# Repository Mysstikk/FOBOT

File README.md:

# FOBOT — Feeding Collaborative Robot

FOBOT es un prototipo de robot colaborativo de seis grados de libertad diseñado para asistir durante la alimentación de personas con movilidad reducida o diversidad funcional.

El sistema combina actuadores Dynamixel, ROS 2, MoveIt 2 y visión artificial para ejecutar una secuencia de recogida de comida y aproximar una cuchara a la boca del usuario mediante control visual.

Este repositorio contiene el código fuente desarrollado para el Trabajo de Fin de Grado:

> *Design and implementation of a collaborative robot for feeding with control through artificial vision*

Autor: Unai Mollá Caballero  
Tutor: Jaime Masiá Vañó  
Universitat Politècnica de València — Campus d'Alcoi  
Curso: 2025–2026

## Características principales

- Control de seis actuadores Dynamixel.
- Integración del hardware mediante `ros2_control`.
- Ejecución de trayectorias articulares previamente configuradas.
- Grabación de posiciones mediante guiado manual.
- Coordinación del comportamiento mediante una máquina de estados finitos.
- Detección facial mediante MediaPipe.
- Reconocimiento de la apertura de la boca y el cierre de los ojos.
- Estimación tridimensional de la posición de la boca.
- Aproximación mediante MoveIt Servo.
- Supervisión de singularidades y colisiones.
- Detección de posibles contactos mediante el esfuerzo de los motores.
- Interfaz física mediante pulsadores e indicadores LED.

## Arquitectura del repositorio

```text
FOBOT/
├── robot_pkg/                 # Control principal, FSM y movimientos
├── fobot_moveit_config/       # Configuración de MoveIt 2
├── fobot_vision/              # Detección facial y control visual
├── singularity_probe/         # Análisis del jacobiano
├── DynamixelSDK               # SDK de los motores Dynamixel
├── dynamixel_interfaces/      # Mensajes y servicios de Dynamixel
├── dynamixel_hardware_interface/
│                              # Integración con ros2_control
└── README.md
```

La estructura puede variar dependiendo de la versión publicada.

## Requisitos

El sistema se ha desarrollado utilizando:

- Ubuntu 22.04.
- ROS 2 Humble.
- Python 3.
- C++.
- MoveIt 2.
- `ros2_control`.
- Dynamixel SDK.
- OpenCV.
- MediaPipe.
- Cámara USB.
- Raspberry Pi 4.

También se necesitan los paquetes de ROS 2 correspondientes a MoveIt Servo, TF2, `usb_cam` y el controlador de trayectorias articulares.

## Instalación

Crear un espacio de trabajo de ROS 2:

```bash
mkdir -p ~/fobot_ws/src
cd ~/fobot_ws/src
```

Clonar el repositorio:

```bash
git clone <URL_DEL_REPOSITORIO>
```

Instalar las dependencias:

```bash
cd ~/fobot_ws
rosdep install --from-paths src --ignore-src -r -y
```

Compilar:

```bash
colcon build --symlink-install
source install/setup.bash
```

La instrucción `source install/setup.bash` debe ejecutarse en cada nueva terminal desde la que se utilice el robot.

## Configuración previa

Antes de iniciar el sistema se debe comprobar:

1. Que cada motor Dynamixel tenga un identificador diferente.
2. Que el puerto serie y la velocidad de comunicación sean correctos.
3. Que la cámara esté conectada y calibrada.
4. Que el plato y el robot estén situados en las posiciones utilizadas durante la configuración.
5. Que la cuchara esté limpia y correctamente fijada.
6. Que no haya obstáculos dentro del espacio de trabajo.

Los parámetros principales se encuentran en los archivos YAML de los paquetes correspondientes.

## Ejecución

Para iniciar el sistema completo:

```bash
ros2 launch robot_pkg FOBOT.launch.py
```

El fichero maestro inicia los controladores, la descripción del robot, la máquina de estados, el sistema de visión y MoveIt Servo.

Después del arranque se debe realizar el movimiento de *homing* antes de comenzar la secuencia de alimentación.

## Grabación de trayectorias

El movimiento automático utiliza una secuencia de posiciones articulares almacenada en un fichero CSV.

El programa de grabación permite:

1. Desactivar el par de los motores.
2. Mover manualmente el brazo.
3. Registrar las posiciones deseadas.
4. Volver a activar el par.
5. Probar la trayectoria antes de utilizarla con comida.

Las primeras pruebas deben realizarse sin situar al usuario dentro del alcance inmediato del robot.

## Funcionamiento general

La secuencia de alimentación es la siguiente:

1. El robot realiza el movimiento de *homing*.
2. El usuario abre la boca para iniciar el ciclo.
3. El robot ejecuta la trayectoria de recogida.
4. La cuchara se desplaza hasta una posición próxima al rostro.
5. El usuario vuelve a abrir la boca para confirmar la entrega.
6. El sistema de visión estima la posición de la boca.
7. MoveIt Servo realiza la aproximación final.
8. El robot regresa para recoger una nueva porción.
9. El usuario puede finalizar el proceso cerrando ambos ojos.

## Limitaciones

El prototipo presenta actualmente las siguientes limitaciones:

- No detecta automáticamente la comida presente en el plato.
- La recogida utiliza trayectorias previamente grabadas.
- El plato debe permanecer en una posición aproximadamente fija.
- La profundidad se estima mediante una cámara RGB monocular.
- El comportamiento puede verse afectado por la iluminación y las oclusiones.
- No se ha realizado una validación clínica ni una certificación de seguridad.
- El sistema debe utilizarse en un entorno controlado y con supervisión.

## Seguridad

Este software pertenece a un prototipo académico y no constituye un producto médico o asistencial certificado.

Antes de utilizarlo:

- Mantener despejado el espacio de trabajo.
- No introducir las manos mientras los motores estén activos.
- Comprobar la temperatura y consistencia de la comida.
- Verificar la fijación de la cuchara.
- No rearmar el sistema sin identificar la causa de la parada.
- Utilizar el interruptor de alimentación si el robot presenta un comportamiento inesperado.

El uso del código y del prototipo se realiza bajo la responsabilidad de la persona que lo instala y opera.

Unai Mollá Caballero

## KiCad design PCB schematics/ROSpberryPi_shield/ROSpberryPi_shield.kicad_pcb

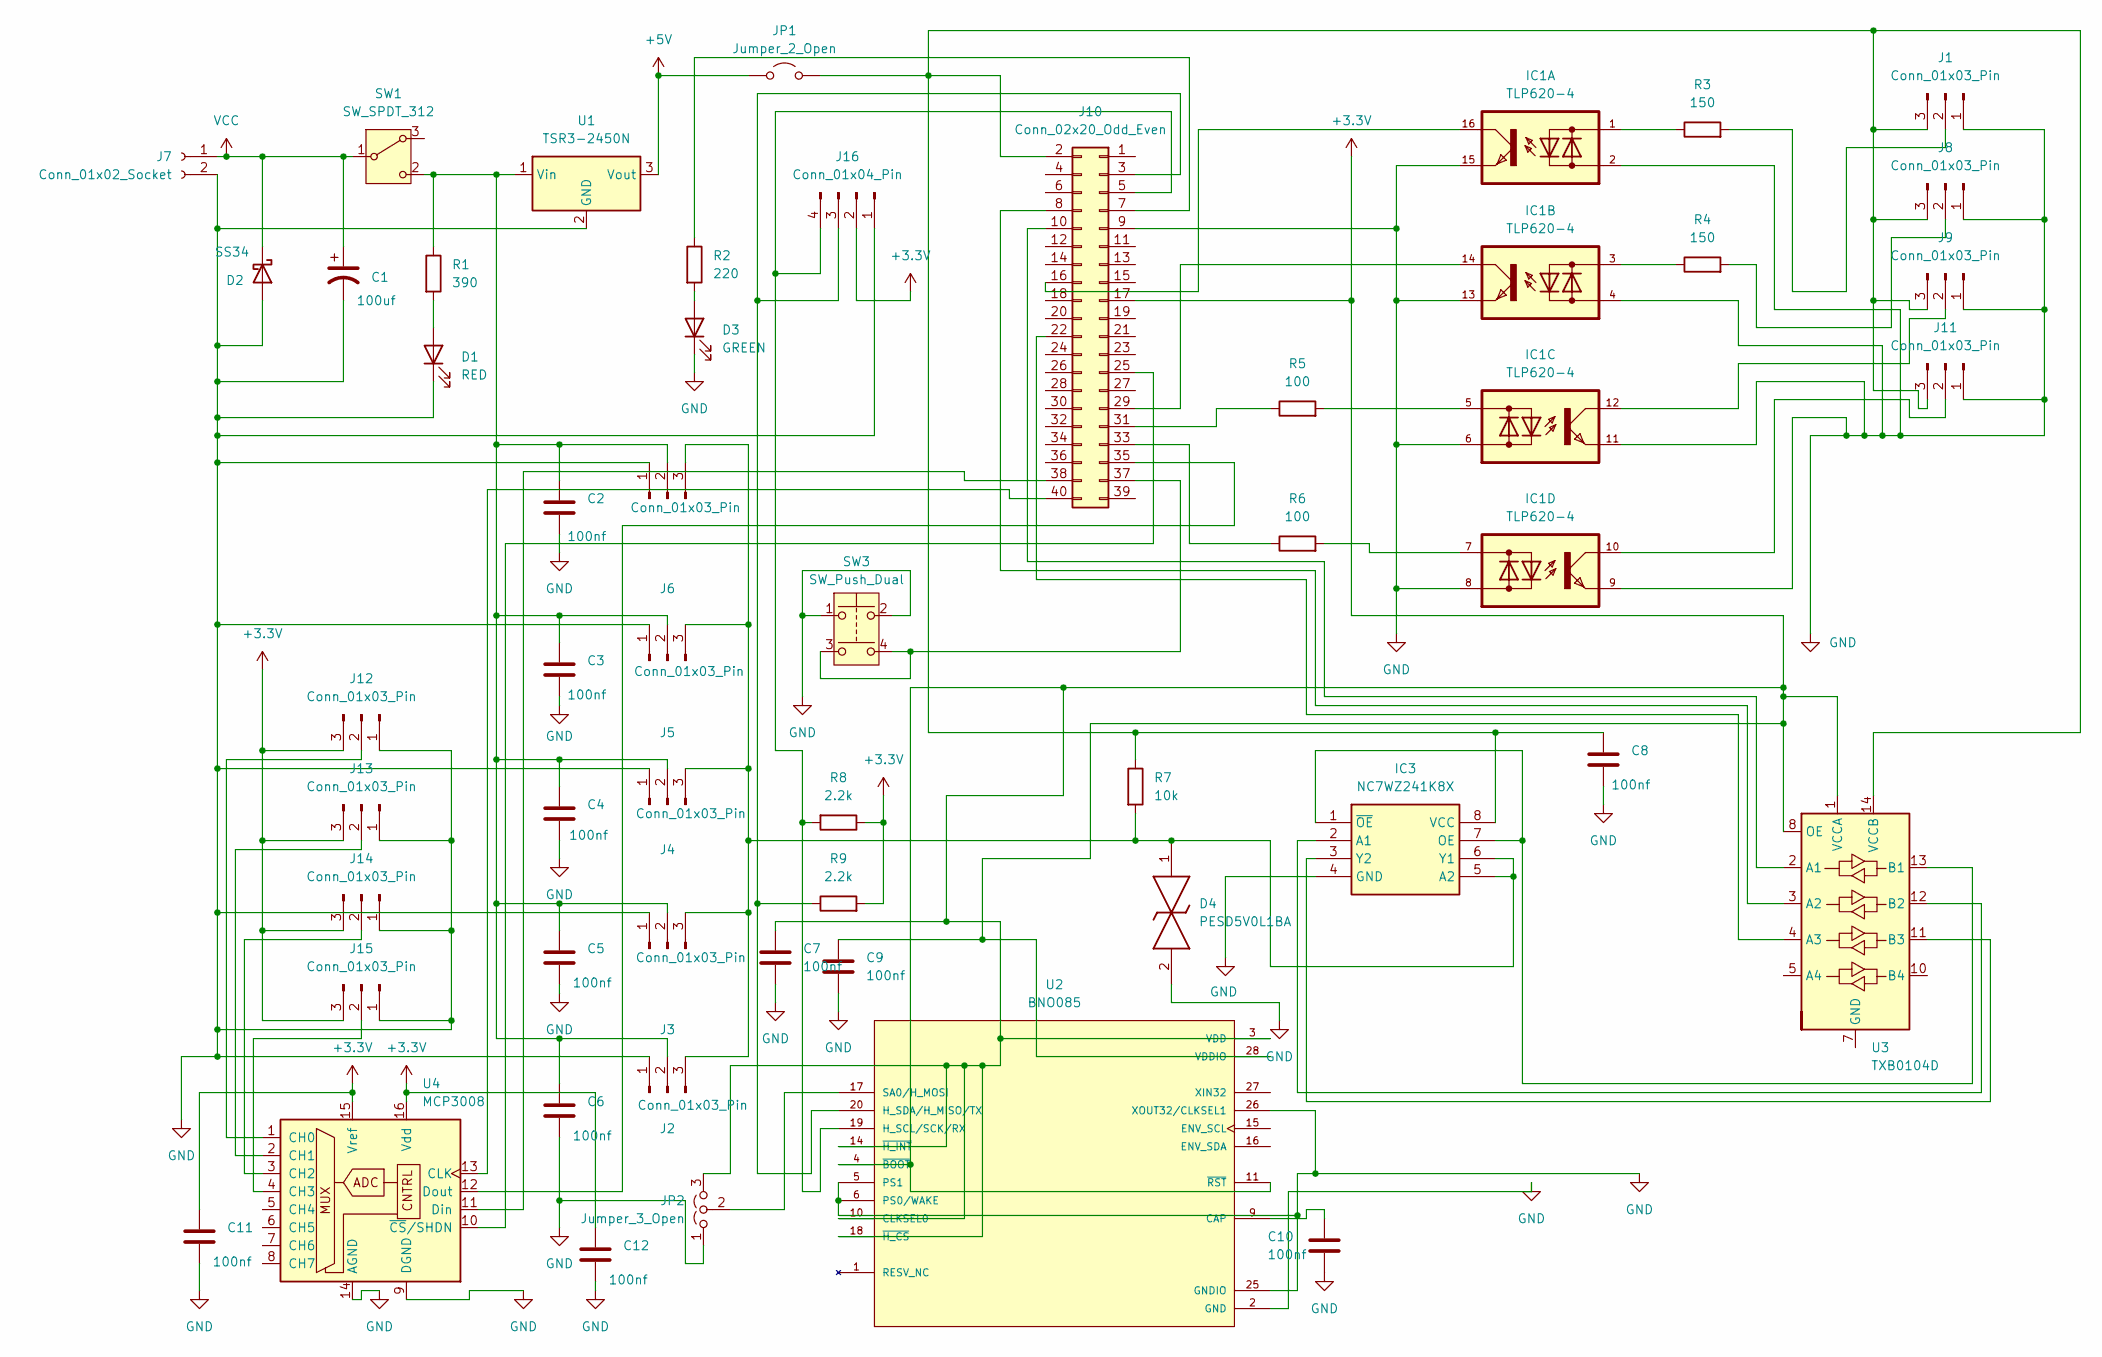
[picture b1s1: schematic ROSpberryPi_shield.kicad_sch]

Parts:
C1: 100uf; CP_Elec_8x10.5
C2, C3, C4, C5, C6, C7, C8, C9, C10, C11, C12: 100nf; CP_EIA-1608-10_AVX-L
D1: RED; LED_0603_1608Metric
D2: SS34; D_DO-201AD_P15.24mm_Horizontal
D3: GREEN; LED_0603_1608Metric
D4: PESD5V0L1BA; SOD2512X110N; Manufacturer_Part_Number PESD5V0L1BA; Mouser Part Number N/A
IC1: TLP620-4; DIP762W60P254L1982H485Q16N
IC3: NC7WZ241K8X; SOP50P310X90-8N; Manufacturer_Part_Number NC7WZ241K8X; Mouser Part Number 512-NC7WZ241K8X
J1, J8, J9, J11, J12, J13, J14, J15: Conn_01x03_Pin; Molex_KK-254_AE-6410-03A_1x03_P2.54mm_Vertical
J2, J3, J4, J5, J6: Conn_01x03_Pin; JST_EH_B3B-EH-A_1x03_P2.50mm_Vertical
J7: Conn_01x02_Socket; TerminalBlock_4Ucon_1x02_P3.50mm_Vertical
J10: Conn_02x20_Odd_Even; PinSocket_2x20_P2.54mm_Vertical
J16: Conn_01x04_Pin; Molex_KK-254_AE-6410-04A_1x04_P2.54mm_Vertical
JP1: Jumper_2_Open; PinHeader_1x02_P2.54mm_Vertical
JP2: Jumper_3_Open; PinHeader_1x03_P2.54mm_Vertical
R1: 390; R_0603_1608Metric
R2: 220; R_0603_1608Metric
R3, R4: 150; R_0603_1608Metric
R5, R6: 100; R_0603_1608Metric
R7: 10k; R_0603_1608Metric
R8, R9: 2.2k; R_0603_1608Metric
SW1: SW_SPDT_312; 500SSP1S1M2QEA
SW3: SW_Push_Dual; DTS62NV
U1: TSR3-2450N; Converter_DCDC_TRACO_TSR2-24xxN_TSR2-24xxxN_THT
U2: BNO085; IC_BNO085; PARTREV v1.17
U3: TXB0104D; SOIC-14_3.9x8.7mm_P1.27mm
U4: MCP3008; DIP-16_W7.62mm

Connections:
+3.3V: C7.1, C9.1, C11.1, C12.1, J10.17, J12.3, J13.3, J14.3, J15.3, J16.2, JP2.3 (B), R8.1, R9.2, U2.3 (VDD), U2.4 (~BOOT), U2.10 (CLKSEL0), U2.11 (~RST), U2.14 (~H_INT), U2.18 (~H_CS), U2.28 (VDDIO), U3.1 (VCCA), U3.8 (OE), U4.15 (Vref), U4.16 (Vdd)
+5V: JP1.1 (A), U1.3 (Vout)
GND: C1.2, C2.2, C3.2, C4.2, C5.2, C6.2, C7.2, C8.2, C9.2, C10.2, C11.2, C12.2, D1.1 (K), D2.2 (A), D3.1 (K), D4.2, IC1.2, IC1.4, IC1.6, IC1.8, IC1.9, IC1.11, IC1.13, IC1.15, IC3.4 (GND), J1.1, J2.1, J3.1, J4.1, J5.1, J6.1, J7.2, J8.1, J9.1, J10.9, J11.1, J12.1, J13.1, J14.1, J15.1, J16.1, JP2.1 (A), SW3.1, SW3.2, U1.2 (GND), U2.2 (GND), U2.5 (PS1), U2.6 (PS0/WAKE), U2.25 (GNDIO), U2.26 (XOUT32/CLKSEL1), U4.9 (DGND), U4.14 (AGND)
unnamed: D1.2 (A), R1.2
unnamed: D3.2 (A), R2.2
unnamed: IC1.1, R3.1
unnamed: IC1.3, R4.1
unnamed: IC1.5, R5.2
unnamed: IC1.7, R6.2
unnamed: IC3.2 (A1), U3.12 (B2)
unnamed: D4.1, IC3.5 (A2), IC3.6 (Y1), J2.3, J3.3, J4.3, J5.3, J6.3, R7.2
unnamed: IC3.1 (~OE), IC3.7 (OE), U3.13 (B1)
unnamed: C8.1, IC3.8 (VCC), J1.3, J8.3, J9.3, J10.2, J11.3, JP1.2 (B), R7.1, U3.14 (VCCB)
unnamed: IC3.3 (Y2), U3.11 (B3)
unnamed: J1.2, R3.2
unnamed: C2.1, C3.1, C4.1, C5.1, C6.1, J2.2, J3.2, J4.2, J5.2, J6.2, R1.1, SW1.2 (C), U1.1 (Vin)
unnamed: J8.2, R4.2
unnamed: IC1.12, J9.2
unnamed: J10.3, J16.3, R9.1, U2.20 (H_SDA/H_MISO/TX)
unnamed: J10.5, J16.4, R8.2, U2.19 (H_SCL/SCK/RX)
unnamed: J10.7, R2.1
unnamed: J10.8, U3.3 (A2)
unnamed: J10.10, U3.2 (A1)
unnamed: IC1.16, J10.16
unnamed: J10.22, U3.4 (A3)
unnamed: J10.25, U4.10 (~CS/SHDN)
unnamed: IC1.14, J10.29
unnamed: J10.31, R5.1
unnamed: J10.33, R6.1
unnamed: J10.35, U4.12 (Dout)
unnamed: J10.37, SW3.3, SW3.4
unnamed: J10.38, U4.11 (Din)
unnamed: J10.40, U4.13 (CLK)
unnamed: IC1.10, J11.2
unnamed: J12.2, U4.1 (CH0)
unnamed: J13.2, U4.2 (CH1)
unnamed: J14.2, U4.3 (CH2)
unnamed: J15.2, U4.4 (CH3)
unnamed: JP2.2 (C), U2.17 (SA0/H_MOSI)
unnamed: C10.1, U2.9 (CAP)
VCC: C1.1, D2.1 (K), J7.1, SW1.1 (B)

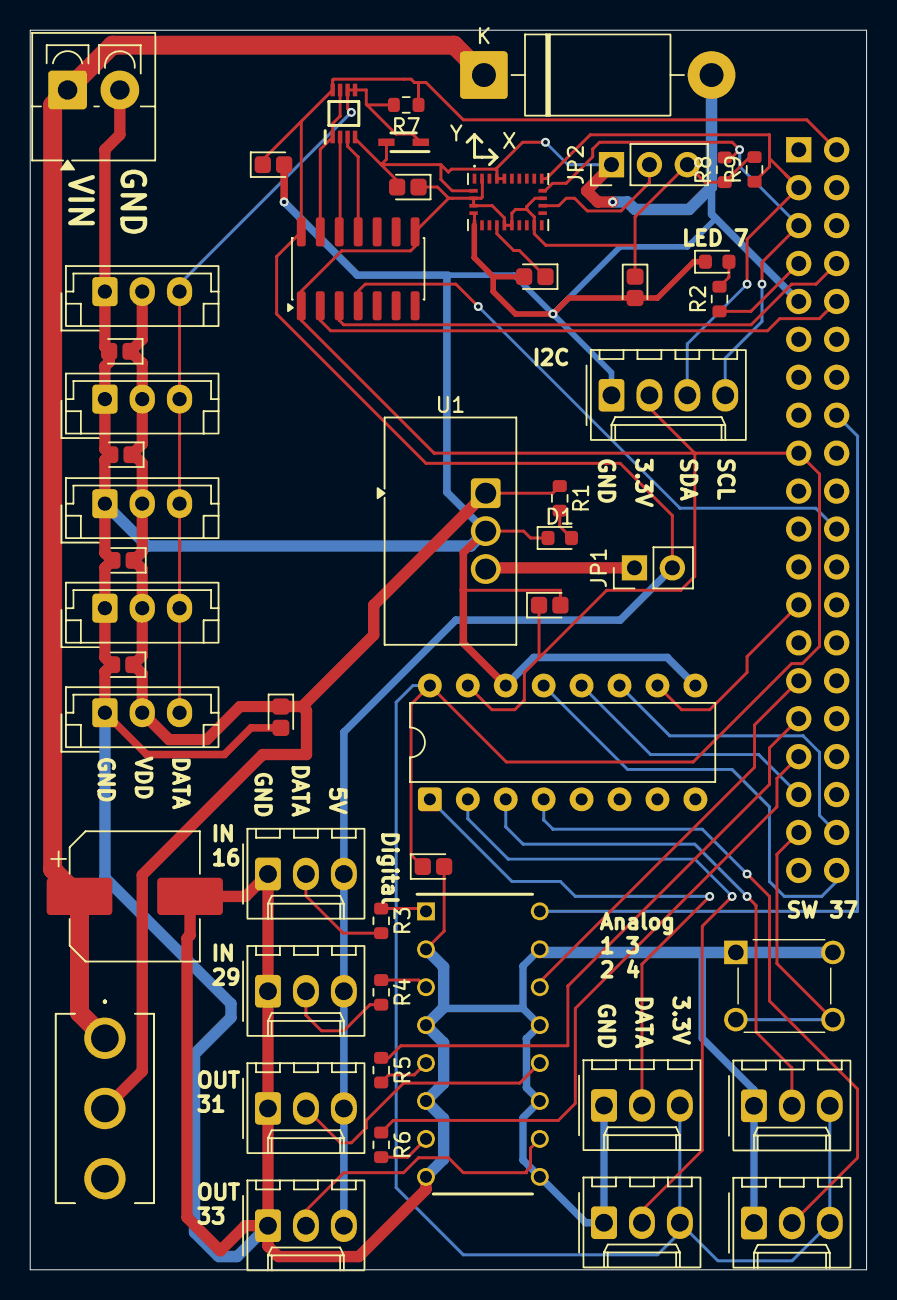
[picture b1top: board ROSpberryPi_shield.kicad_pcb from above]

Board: 2 copper layers, 56.0 x 83.0 mm, 51 parts (1 on the bottom side), 41 nets.
